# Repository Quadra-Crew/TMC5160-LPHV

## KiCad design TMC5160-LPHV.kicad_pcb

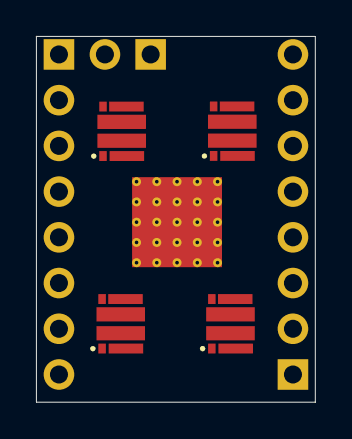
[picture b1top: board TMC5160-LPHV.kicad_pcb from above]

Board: 4 copper layers, 15.5 x 20.3 mm, 8 parts (1 on the bottom side), 12 nets, no tracks yet.

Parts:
J1: StepStick Left; PinHeader_1x08_P2.54mm_Vertical
J2: StepStick Right; PinHeader_1x08_P2.54mm_Vertical
J3: StepStick Diag; PinHeader_1x02_P2.54mm_Vertical
Q1, Q2, Q3, Q4: DMT6018LDR; V-DFN3030-8 (Type H)
U1: TMC5160A-TA; TQFP-48-1EP_7x7mm_P0.5mm_EP5x5mm_ThermalVias

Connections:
/CFG0: J1.5, U1.16 (SDO/CFG0)
/CFG1: J1.2, U1.15 (SDI/CFG1)
/CFG2: J1.3, U1.14 (SCK/CFG2)
/CFG3: J1.4, U1.13 (~CS/CFG3)
/DIAG0: J3.2, U1.26 (SWN/DIAG0)
/DIAG1: J3.1, U1.27 (SWP/DIAG1)
/DIR: J1.8, U1.18 (REFR/DIR)
/EN: J1.1, U1.28 (~DRV_EN)
/STEP: J1.7, U1.17 (REFL/STEP)
/VIO: J2.2, U1.20 (VCC_IO)
/VMOT: J2.8, U1.4 (VSA), U1.33 (VS)
GND: J2.1, J2.7, U1.6 (GNDA), U1.11 (TST_MODE), U1.12 (CLK), U1.19 (GNDD), U1.21 (SD_MODE), U1.22 (SPI_MODE), U1.30 (GNDD)

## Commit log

2024-08-16 fix submodule url
2024-08-16 use http for submodule
2024-08-16 switch to four-layer, minor improvements
